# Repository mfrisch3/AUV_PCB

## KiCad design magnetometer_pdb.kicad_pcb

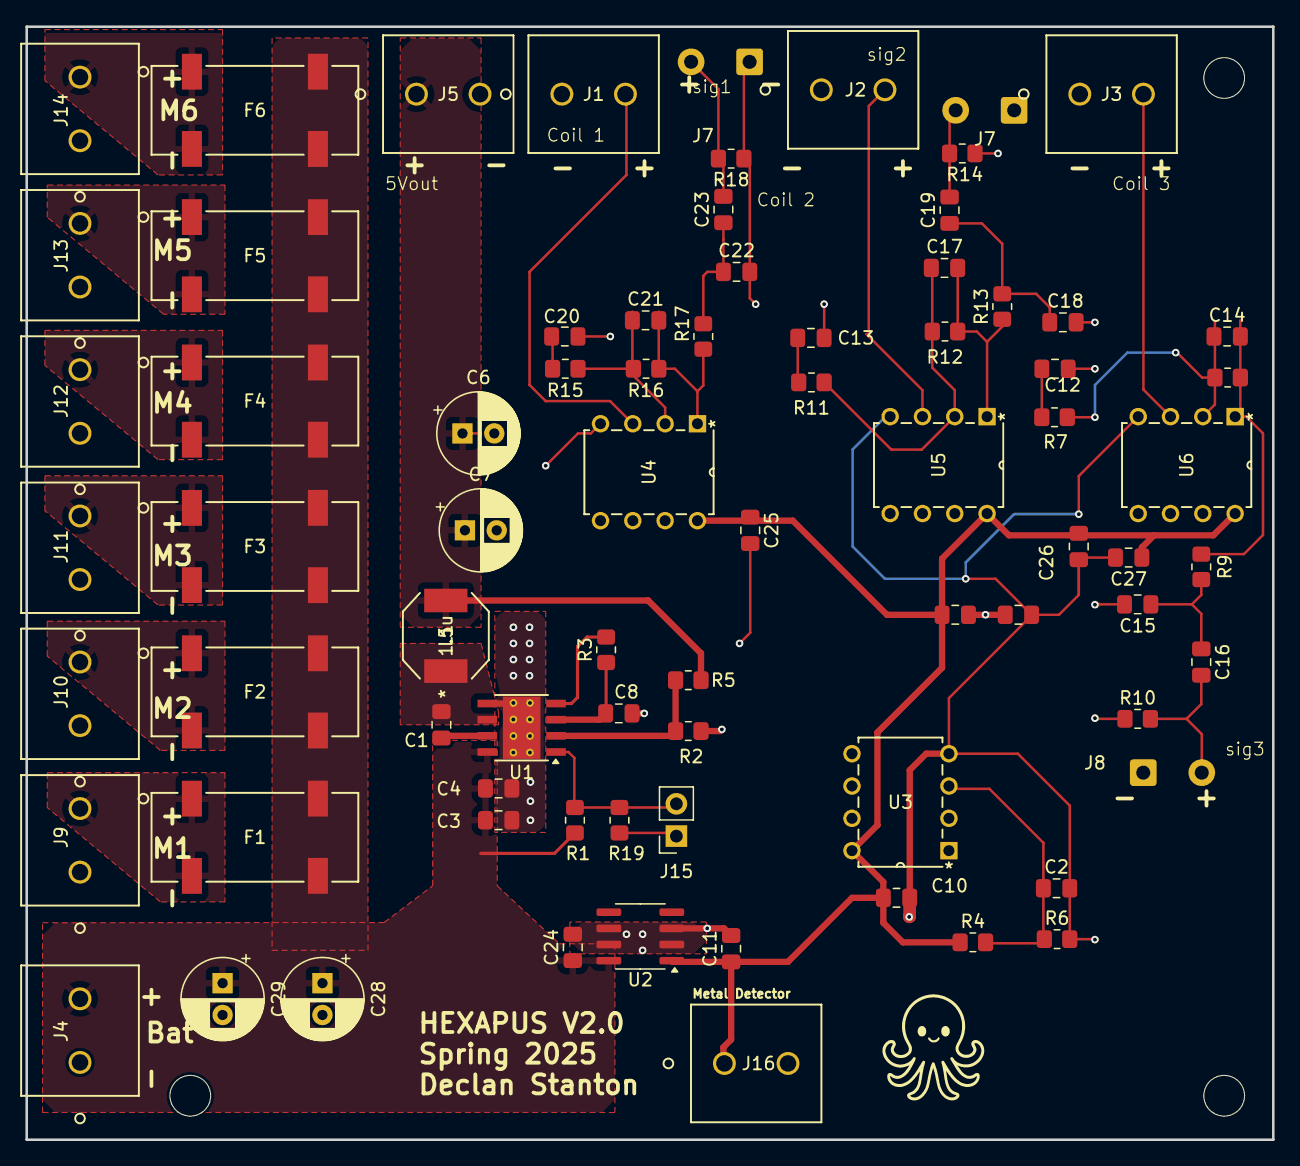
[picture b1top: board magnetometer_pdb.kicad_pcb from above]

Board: 2 copper layers, 98.0 x 87.5 mm, 77 parts (0 on the bottom side), 36 nets.

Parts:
C1: 0.1u; C_0805_2012Metric_Pad1.18x1.45mm_HandSolder
C2, C14, C17, C21: .1u; C_0805_2012Metric_Pad1.18x1.45mm_HandSolder
C3, C4, C5, C9, C10, C11, C24: 10u; C_0805_2012Metric_Pad1.18x1.45mm_HandSolder
C6, C7: 22u; CP_Radial_D6.3mm_P2.50mm
C8: .47u; C_0805_2012Metric_Pad1.18x1.45mm_HandSolder
C12, C13, C20: 1.6u; C_0805_2012Metric_Pad1.18x1.45mm_HandSolder
C15, C16, C18, C19, C22, C23, C25, C26, C27: 2.2u; C_0805_2012Metric_Pad1.18x1.45mm_HandSolder
C28: 100u; CP_Radial_D6.3mm_P2.50mm
C29: C_Polarized_US; CP_Radial_D6.3mm_P2.50mm
F1, F2, F3, F4, F5, F6: Fuse; fuse_holder
J1, J2, J3, J4, J5, J9, J10, J11, J12, J13, J14, J16: Screw_Terminal_01x02; 2_Pin_Screw_Term
J6, J7, J8: Conn_01x02_Pin; SolderWire-0.5sqmm_1x02_P4.6mm_D0.9mm_OD2.1mm
J15: Conn_01x02_Pin; PinSocket_1x02_P2.54mm_Vertical
L1: 1.5u; SPM6530T-1R5M100
R1: 47k; R_0805_2012Metric_Pad1.20x1.40mm_HandSolder
R2: 365k; R_0805_2012Metric_Pad1.20x1.40mm_HandSolder
R3: 100k; R_0805_2012Metric_Pad1.20x1.40mm_HandSolder
R4, R6, R19: 10k; R_0805_2012Metric_Pad1.20x1.40mm_HandSolder
R5: 49.9k; R_0805_2012Metric_Pad1.20x1.40mm_HandSolder
R7, R9, R10, R11, R13, R14, R15, R17, R18: 1k; R_0805_2012Metric_Pad1.20x1.40mm_HandSolder
R8, R12, R16: 200k; R_0805_2012Metric_Pad1.20x1.40mm_HandSolder
U1: TPS56528DDA; Texas_HSOP-8-1EP_3.9x4.9mm_P1.27mm_ThermalVias
U2: L78L09_SO8; SOIC-8_3.9x4.9mm_P1.27mm
U3, U4, U5, U6: TL072ACP

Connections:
5V_OUT: C6.1, C7.1, J5.1, L1.2, R5.1
+BATT: C3.1, C4.1, C24.1, C28.1, C29.1, F1.2, F2.2, F3.2, F4.2, F5.2, F6.2, J4.2, R1.2, U1.8 (VIN), U2.8 (IN)
/3_AX_Magnetometer/C1_IN: J1.2, U4.3 (+)
/3_AX_Magnetometer/C2_IN: J2.2, U5.3 (+)
/3_AX_Magnetometer/C3_IN: J3.2, U6.3 (+)
/5v Power Supply/BK_SW: C1.1, L1.1, U1.6 (SW)
/12_9_Linear_Reg/9V_OUT: C9.1, C10.1, C11.1, C25.1, C26.1, C27.1, J16.1, R4.1, U2.1 (OUT), U3.8 (V+), U4.8 (V+), U5.8 (V+), U6.8 (V+)
/12_9_Linear_Reg/V_GND: C5.1, C9.2, C12.1, C13.1, C15.2, C18.2, C20.1, C22.2, J1.1, J2.1, J3.1, J6.1, J7.1, J8.1, R10.1, R14.1, R18.1, U3.1, U3.2 (-)
/C1_OUT: C23.2, J6.2, R18.2
/C2_OUT: C19.2, J7.2, R14.2
/C3_OUT: C16.2, J8.2, R10.2
/M1_OUT: F1.1, J9.2
/M2_OUT: F2.1, J10.2
/M3_OUT: F3.1, J11.2
/M4_OUT: F4.1, J12.2
/M5_OUT: F5.1, J13.2
/M6_OUT: F6.1, J14.2
Bat_GND: C2.2, C3.2, C4.2, C5.2, C6.2, C7.2, C8.1, C10.2, C11.2, C24.2, C25.2, C26.2, C27.2, C28.2, C29.2, J4.1, J5.2, J9.1, J10.1, J11.1, J12.1, J13.1, J14.1, J15.1, J16.2, R2.1, R6.2, R19.2, U1.5 (GND), U1.9 (GND), U2.2 (GND), U2.3 (GND), U2.6 (GND), U2.7 (GND), U3.4 (V-), U4.4 (V-), U5.4 (V-), U6.4 (V-)
unnamed: C12.2, R7.1
unnamed: C13.2, R11.1
unnamed: C14.2, R8.2, R9.1, U6.1
unnamed: C15.1, C16.1, R9.2
unnamed: C17.2, R12.2, R13.1, U5.1
unnamed: C18.1, C19.1, R13.2
unnamed: C20.2, R15.1
unnamed: C21.2, R16.2, R17.1, U4.1
unnamed: C22.1, C23.1, R17.2
unnamed: J15.2, R1.1, R19.1, U1.1 (EN)
unnamed: R3.2, U1.4 (PG)
unnamed: C1.2, U1.7 (VBST)
unnamed: R2.2, R5.2, U1.2 (VFB)
unnamed: C8.2, R3.1, U1.3 (VREG5)
unnamed: C2.1, R4.2, R6.1, U3.3 (+)
unnamed: C21.1, R15.2, R16.1, U4.2 (-)
unnamed: C17.1, R11.2, R12.1, U5.2 (-)
unnamed: C14.1, R7.2, R8.1, U6.2 (-)

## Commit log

2025-04-09 PCB V2
2025-04-09 changed vias
2025-04-09 Modified schematic and pcb
2025-04-09 Added decoupling caps
2025-04-09 Adjusted caps
2025-04-11 Cleaned up PCB and added Fuses
2025-04-13 Simplified Schematic and finished PCB
2025-04-13 Added bypass caps for 5V output and battery to protect from in rush and back emf

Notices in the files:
parts and their libraries:
Copyright 2016 Accelerated Designs. All rights reserved.
